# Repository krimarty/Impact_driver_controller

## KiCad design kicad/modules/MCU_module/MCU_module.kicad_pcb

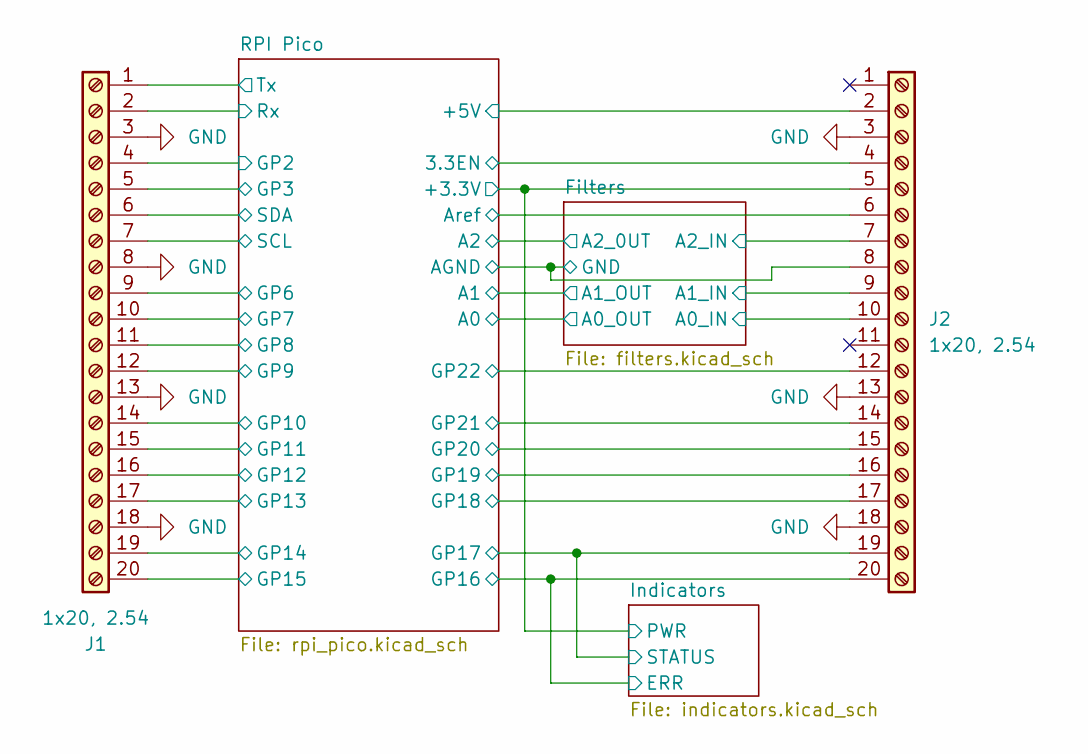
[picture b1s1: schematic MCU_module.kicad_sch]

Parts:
J1, J2: 1x20, 2.54; PinHeader_1x20_P2.54mm_Vertical; Manufacturer Part Number 68000-420HLF; Mouser number 649-68000-420HLF

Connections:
/Filters/A0_IN: J2.10; also elsewhere on the board
/Filters/A1_IN: J2.9; also elsewhere on the board
/Filters/A2_IN: J2.7; also elsewhere on the board
/Filters/GND: J2.8; also elsewhere on the board
/Indicators/ERR: J2.20; also elsewhere on the board
/Indicators/PWR: J2.5; also elsewhere on the board
/Indicators/STATUS: J2.19; also elsewhere on the board
/RPI Pico/3.3EN: J2.4; also elsewhere on the board
/RPI Pico/+5V: J2.2; also elsewhere on the board
/RPI Pico/Aref: J2.6; also elsewhere on the board
/RPI Pico/GP2: J1.4; also elsewhere on the board
/RPI Pico/GP3: J1.5; also elsewhere on the board
/RPI Pico/GP6: J1.9; also elsewhere on the board
/RPI Pico/GP7: J1.10; also elsewhere on the board
/RPI Pico/GP8: J1.11; also elsewhere on the board
/RPI Pico/GP9: J1.12; also elsewhere on the board
/RPI Pico/GP10: J1.14; also elsewhere on the board
/RPI Pico/GP11: J1.15; also elsewhere on the board
/RPI Pico/GP12: J1.16; also elsewhere on the board
/RPI Pico/GP13: J1.17; also elsewhere on the board
/RPI Pico/GP14: J1.19; also elsewhere on the board
/RPI Pico/GP15: J1.20; also elsewhere on the board
/RPI Pico/GP18: J2.17; also elsewhere on the board
/RPI Pico/GP19: J2.16; also elsewhere on the board
/RPI Pico/GP20: J2.15; also elsewhere on the board
/RPI Pico/GP21: J2.14; also elsewhere on the board
/RPI Pico/GP22: J2.12; also elsewhere on the board
/RPI Pico/Rx: J1.2; also elsewhere on the board
/RPI Pico/SCL: J1.7; also elsewhere on the board
/RPI Pico/SDA: J1.6; also elsewhere on the board
/RPI Pico/Tx: J1.1; also elsewhere on the board
GND: J1.3, J1.8, J1.13, J1.18, J2.3, J2.13, J2.18; also elsewhere on the board

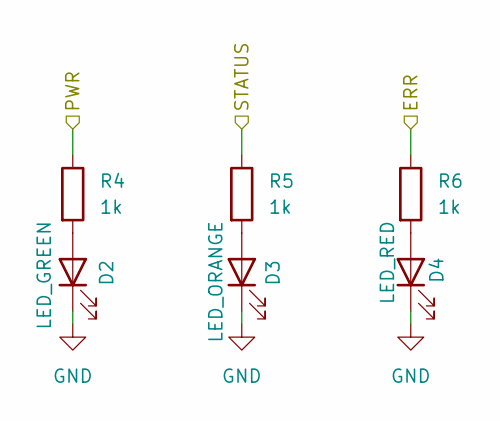
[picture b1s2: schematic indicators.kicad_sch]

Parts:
D2: LED_GREEN; LED_0805_2012Metric_Pad1.15x1.40mm_HandSolder; Manufacturer Part Number APTD2012LCGCK; Mouser number 604-APTD2012LCGCK
D3: LED_ORANGE; LED_0805_2012Metric_Pad1.15x1.40mm_HandSolder; Manufacturer Part Number APTD2012LSYCK; Mouser number 604-APTD2012LSYCK
D4: LED_RED; LED_0805_2012Metric_Pad1.15x1.40mm_HandSolder; Manufacturer Part Number APTD2012LSURCK; Mouser number 604-APTD2012LSURCK
R4, R5, R6: 1k; R_0603_1608Metric_Pad0.98x0.95mm_HandSolder; Manufacturer Part Number RC0603FR-071KL; Mouser number 603-RC0603FR-071KL

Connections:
/Indicators/ERR: R6.1; also elsewhere on the board
/Indicators/PWR: R4.1; also elsewhere on the board
/Indicators/STATUS: R5.1; also elsewhere on the board
GND: D2.1 (K), D3.1 (K), D4.1 (K); also elsewhere on the board
unnamed: D2.2 (A), R4.2
unnamed: D3.2 (A), R5.2
unnamed 38: D4.2 (A), R6.2; also elsewhere on the board

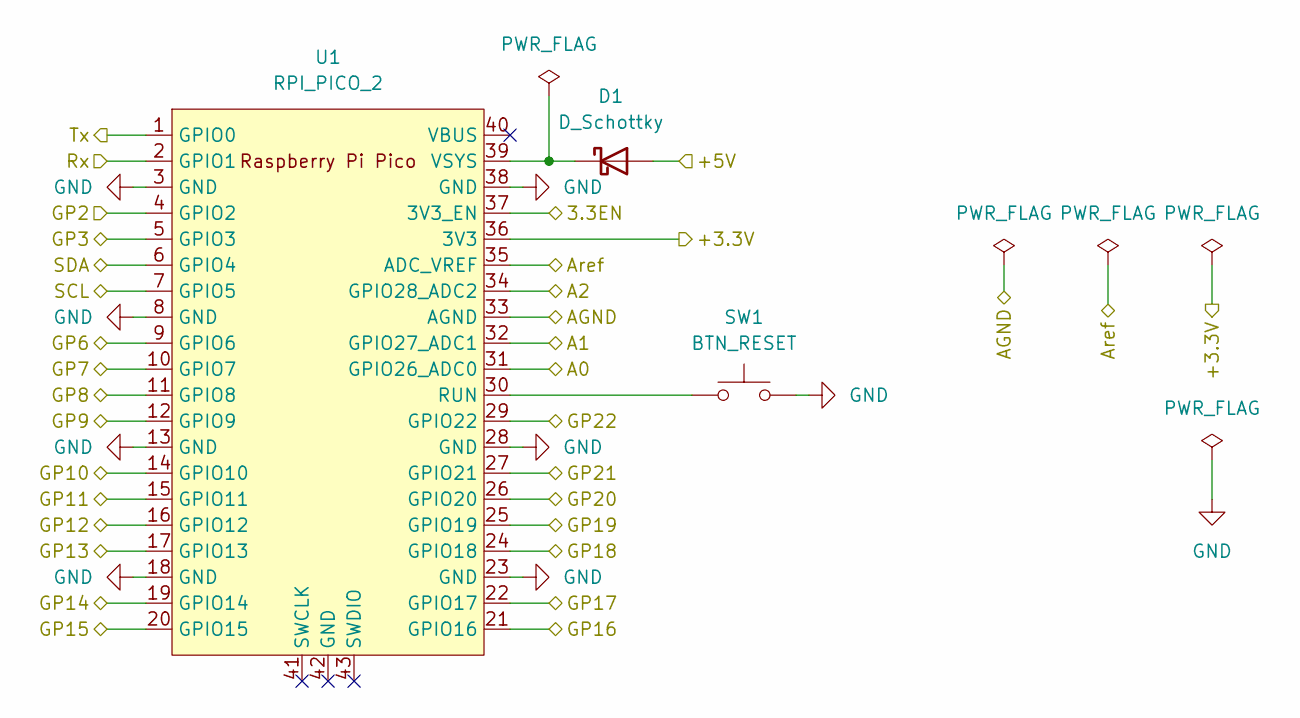
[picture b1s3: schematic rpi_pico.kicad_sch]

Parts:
D1: D_Schottky; D_0805_2012Metric_Pad1.15x1.40mm_HandSolder; Manufacturer Part Number SD0805S020S0R5; Mouser number 581-SD0805S020S0R5
SW1: BTN_RESET; SW_Tactile_SPST_NO_Straight_CK_PTS636Sx25SMTRLFS; Manufacturer Part Number TS09-63-25-WT-160-SMT-TR; Mouser number 179-TS0925WT160SMTTR
U1: RPI_PICO_2; RPi_Pico_SMD_TH; Manufacturer Part Number SC1631; Mouser number 358-SC1631

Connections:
/Filters/A0_OUT: U1.31 (GPIO26_ADC0); also elsewhere on the board
/Filters/A1_OUT: U1.32 (GPIO27_ADC1); also elsewhere on the board
/Filters/A2_0UT: U1.34 (GPIO28_ADC2); also elsewhere on the board
/Filters/GND: U1.33 (AGND); also elsewhere on the board
/Indicators/ERR: U1.21 (GPIO16); also elsewhere on the board
/Indicators/PWR: U1.36 (3V3); also elsewhere on the board
/Indicators/STATUS: U1.22 (GPIO17); also elsewhere on the board
/RPI Pico/3.3EN: U1.37 (3V3_EN); also elsewhere on the board
/RPI Pico/+5V: D1.2 (A); also elsewhere on the board
/RPI Pico/Aref: U1.35 (ADC_VREF); also elsewhere on the board
/RPI Pico/GP2: U1.4 (GPIO2); also elsewhere on the board
/RPI Pico/GP3: U1.5 (GPIO3); also elsewhere on the board
/RPI Pico/GP6: U1.9 (GPIO6); also elsewhere on the board
/RPI Pico/GP7: U1.10 (GPIO7); also elsewhere on the board
/RPI Pico/GP8: U1.11 (GPIO8); also elsewhere on the board
/RPI Pico/GP9: U1.12 (GPIO9); also elsewhere on the board
/RPI Pico/GP10: U1.14 (GPIO10); also elsewhere on the board
/RPI Pico/GP11: U1.15 (GPIO11); also elsewhere on the board
/RPI Pico/GP12: U1.16 (GPIO12); also elsewhere on the board
/RPI Pico/GP13: U1.17 (GPIO13); also elsewhere on the board
/RPI Pico/GP14: U1.19 (GPIO14); also elsewhere on the board
/RPI Pico/GP15: U1.20 (GPIO15); also elsewhere on the board
/RPI Pico/GP18: U1.24 (GPIO18); also elsewhere on the board
/RPI Pico/GP19: U1.25 (GPIO19); also elsewhere on the board
/RPI Pico/GP20: U1.26 (GPIO20); also elsewhere on the board
/RPI Pico/GP21: U1.27 (GPIO21); also elsewhere on the board
/RPI Pico/GP22: U1.29 (GPIO22); also elsewhere on the board
/RPI Pico/Rx: U1.2 (GPIO1); also elsewhere on the board
/RPI Pico/SCL: U1.7 (GPIO5); also elsewhere on the board
/RPI Pico/SDA: U1.6 (GPIO4); also elsewhere on the board
/RPI Pico/Tx: U1.1 (GPIO0); also elsewhere on the board
GND: SW1.2, U1.3 (GND), U1.8 (GND), U1.13 (GND), U1.18 (GND), U1.23 (GND), U1.28 (GND), U1.38 (GND); also elsewhere on the board
unnamed: D1.1 (K), U1.39 (VSYS)
unnamed: SW1.1, U1.30 (RUN)

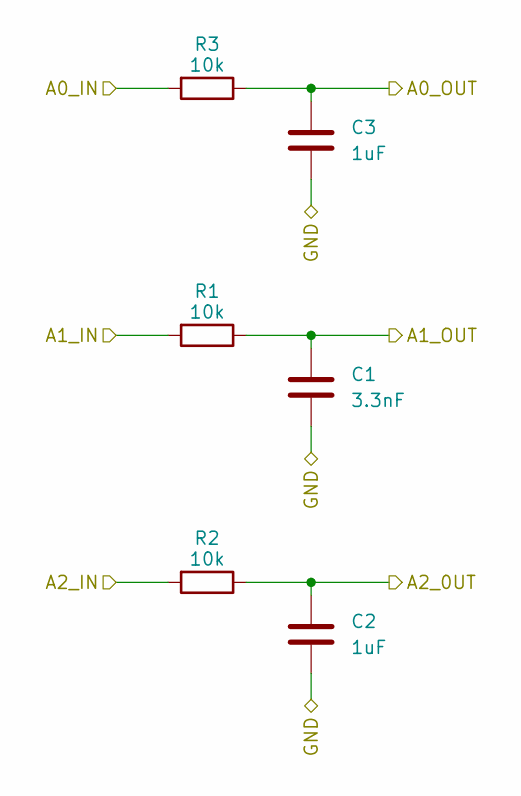
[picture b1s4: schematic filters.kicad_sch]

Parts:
C1: 3.3nF; C_0603_1608Metric_Pad1.08x0.95mm_HandSolder; Manufacturer Part Number VJ0603Y332KXBAC; Mouser number 77-VJ0603Y332KXBAC
C2, C3: 1uF; C_1206_3216Metric_Pad1.33x1.80mm_HandSolder; Manufacturer Part Number CC603KRX5R8BB105; Mouser number 603-CC603KRX5R8BB105
R1, R2, R3: 10k; R_0603_1608Metric_Pad0.98x0.95mm_HandSolder; Manufacturer Part Number RC0603FR-0710KL; Mouser number 603-RC0603FR-0710KL

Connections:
/Filters/A0_IN: R3.2; also elsewhere on the board
/Filters/A0_OUT: C3.1, R3.1; also elsewhere on the board
/Filters/A1_IN: R1.2; also elsewhere on the board
/Filters/A1_OUT: C1.1, R1.1; also elsewhere on the board
/Filters/A2_0UT: C2.1, R2.1; also elsewhere on the board
/Filters/A2_IN: R2.2; also elsewhere on the board
/Filters/GND: C1.2, C2.2, C3.2; also elsewhere on the board

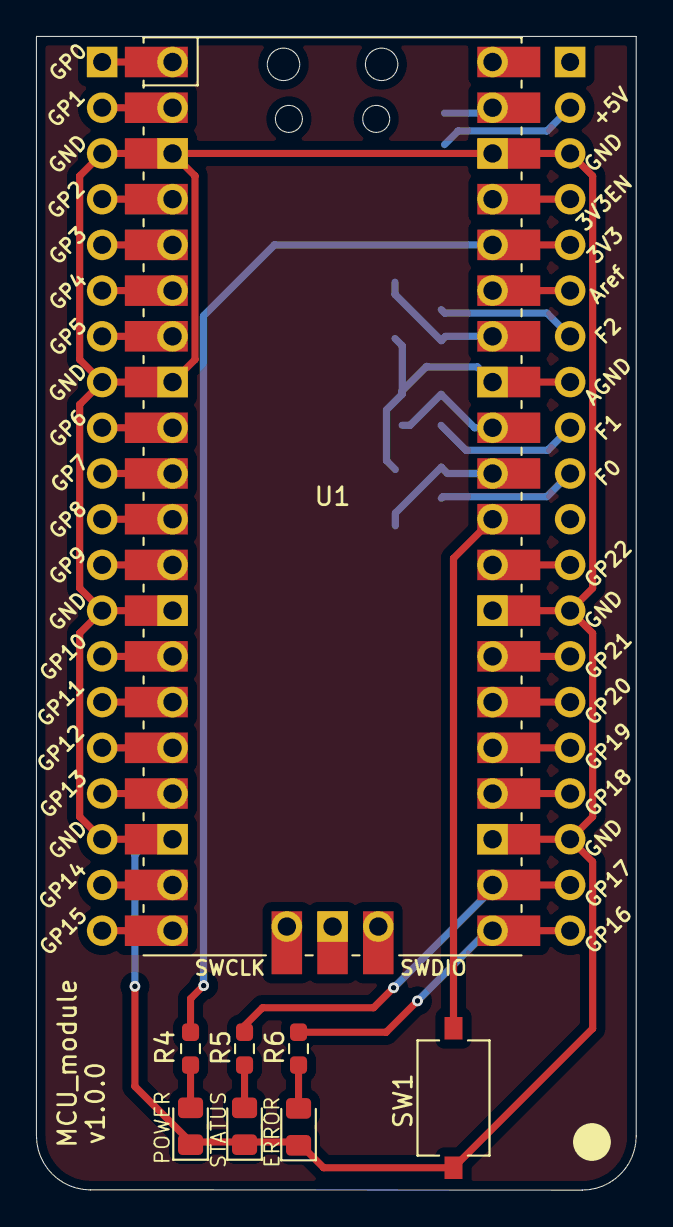
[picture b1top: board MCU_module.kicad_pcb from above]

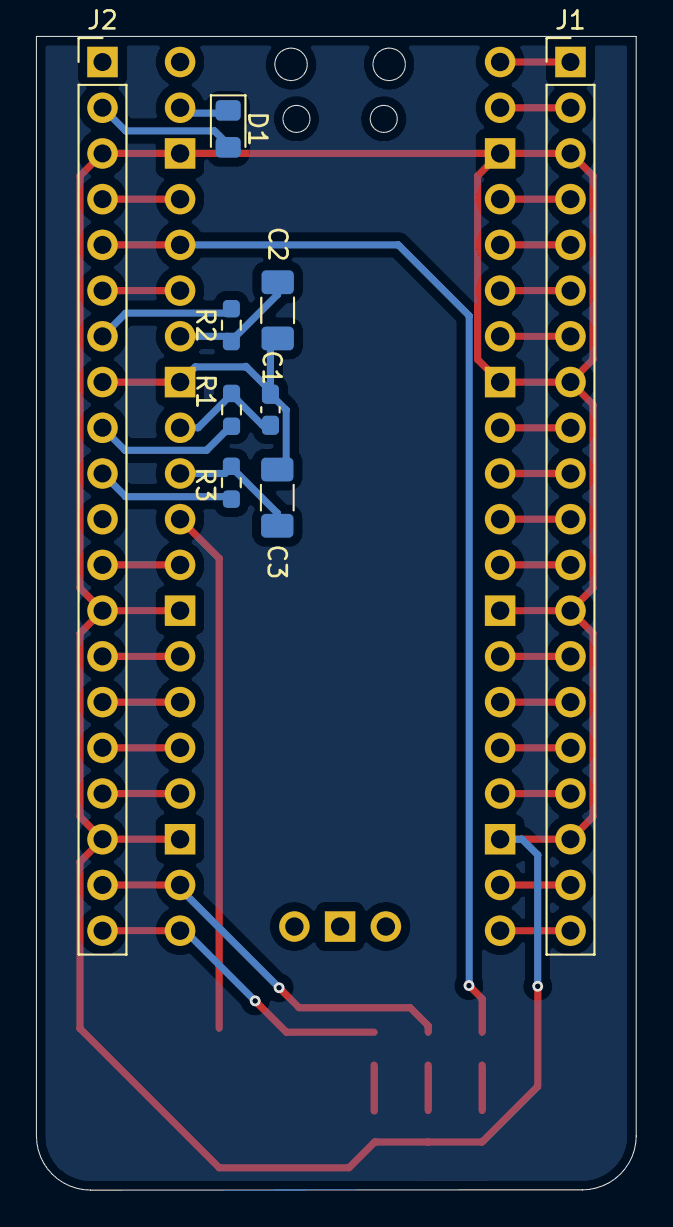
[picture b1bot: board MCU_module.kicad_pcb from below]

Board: 2 copper layers, 33.3 x 64.1 mm, 17 parts (9 on the bottom side), 40 nets.

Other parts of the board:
ERROR: LED_RED; LED_0805_2012Metric_Pad1.15x1.40mm_HandSolder

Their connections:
GND: ERROR.1 (K); also elsewhere on the board
unnamed 38: ERROR.2 (A); also elsewhere on the board

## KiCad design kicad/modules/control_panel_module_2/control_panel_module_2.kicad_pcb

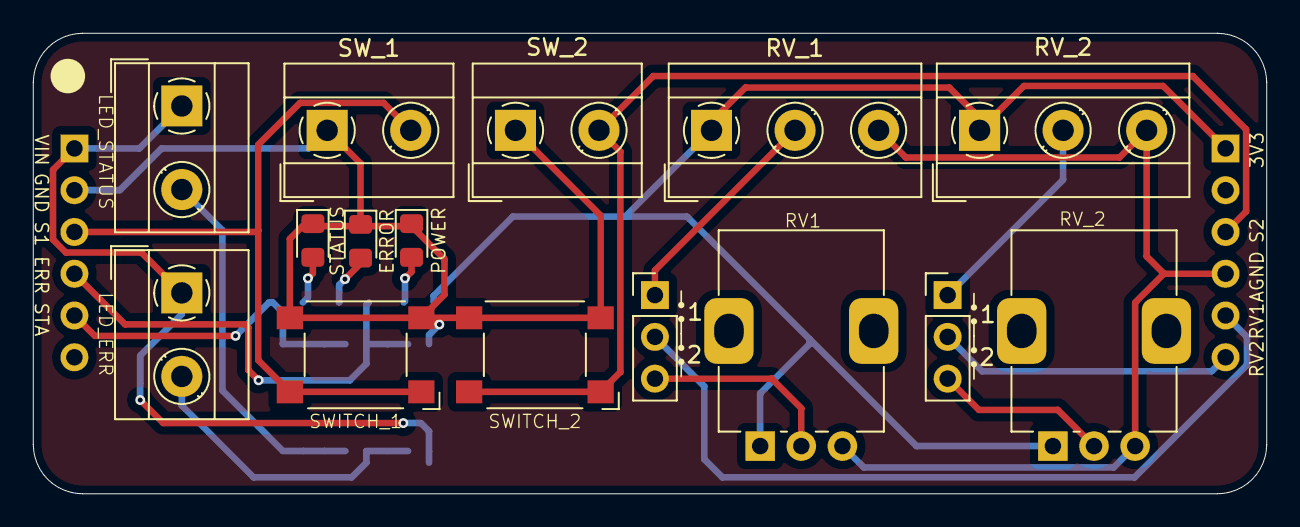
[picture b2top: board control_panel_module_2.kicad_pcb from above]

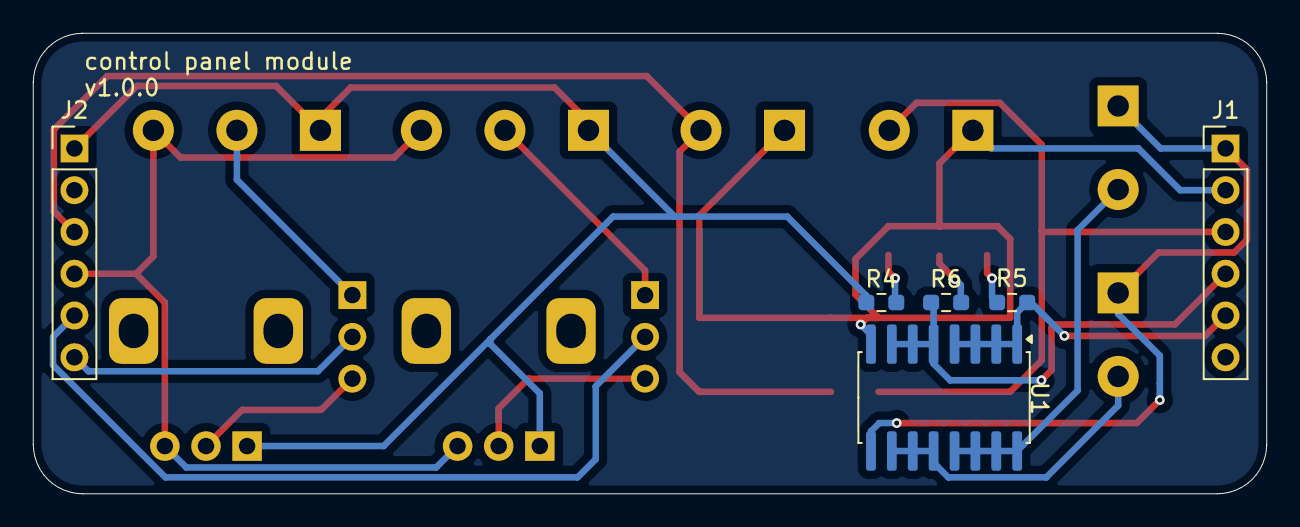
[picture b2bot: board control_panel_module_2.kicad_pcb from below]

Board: 2 copper layers, 75.0 x 28.0 mm, 21 parts (6 on the bottom side), 19 nets.

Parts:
ERROR: LED_RED; LED_0805_2012Metric_Pad1.15x1.40mm_HandSolder
J1, J2: 1x6 2.54; PinHeader_1x06_P2.54mm_Vertical
J3: 1x3 5.08; TerminalBlock_MetzConnect_Type101_RT01603HBWC_1x03_P5.08mm_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
J5, J7, J8: 1x2 5.08; TerminalBlock_MetzConnect_Type101_RT01602HBWC_1x02_P5.08mm_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
JP1, JP2: 1x3 2.54; PinHeader_1x03_P2.54mm_Vertical
POWER: LED_GREEN; LED_0805_2012Metric_Pad1.15x1.40mm_HandSolder
R4, R5, R6: 1k; R_0603_1608Metric_Pad0.98x0.95mm_HandSolder
RV1, RV2: 100k; Potentiometer_Alps_RK09K_Single_Vertical
RV_2: 1x3 5.08; TerminalBlock_MetzConnect_Type101_RT01603HBWC_1x03_P5.08mm_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
STATUS: LED_ORANGE; LED_0805_2012Metric_Pad1.15x1.40mm_HandSolder
SW2: BTN; SW_SPST_Omron_B3FS-105xP
SWITCH_1: BTN; SW_SPST_Omron_B3FS-105xP
SW_2: 1x2 5.08; TerminalBlock_MetzConnect_Type101_RT01602HBWC_1x02_P5.08mm_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
U1: ULN2004A; SOIC-16W_5.3x10.2mm_P1.27mm

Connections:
+3.3V: J2.1, J3.1, R4.1, RV1.1, RV2.1, RV_2.1
+Vin: J1.1, J7.1, J8.1, U1.9 (COM)
/Buttons/RV_1: J2.5, JP1.2 (C)
/Buttons/RV_2: J2.6, JP2.2 (C)
/Buttons/SW_1: J1.3, J5.2, SWITCH_1.1 (A)
/Buttons/SW_2: J2.3, SW2.1 (A), SW_2.2
/Indicators/ERR: J1.4, R6.1, U1.5 (I5), U1.6 (I6), U1.7 (I7)
/Indicators/STATUS: J1.5, R5.1, U1.1 (I1), U1.2 (I2), U1.3 (I3), U1.4 (I4)
AGND: J2.4, J3.3, RV1.3, RV2.3, RV_2.3
GND: ERROR.1 (K), J1.2, J5.1, POWER.1 (K), STATUS.1 (K), SW2.2 (B), SWITCH_1.2 (B), SW_2.1, U1.8 (GND)
unnamed: POWER.2 (A), R4.2
unnamed: R5.2, STATUS.2 (A)
unnamed: ERROR.2 (A), R6.2
unnamed: J3.2, JP1.1 (A)
unnamed: JP2.1 (A), RV_2.2
unnamed: J7.2, U1.13 (O4), U1.14 (O3), U1.15 (O2), U1.16 (O1)
unnamed: J8.2, U1.10 (O7), U1.11 (O6), U1.12 (O5)
unnamed: JP1.3 (B), RV1.2
unnamed: JP2.3 (B), RV2.2

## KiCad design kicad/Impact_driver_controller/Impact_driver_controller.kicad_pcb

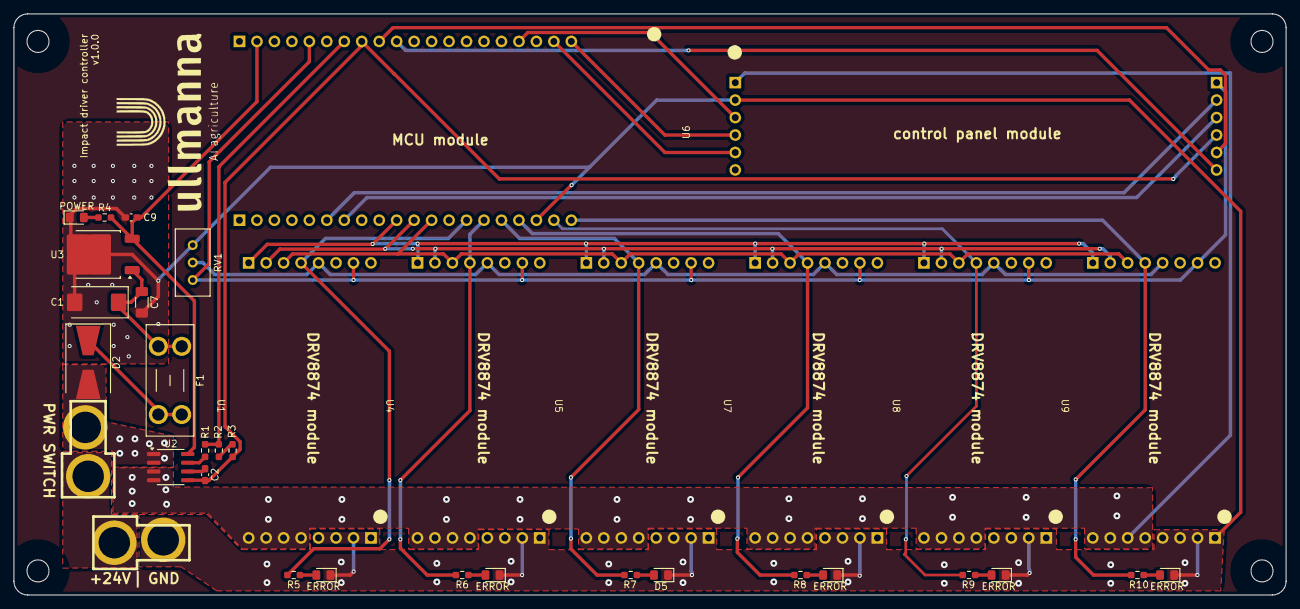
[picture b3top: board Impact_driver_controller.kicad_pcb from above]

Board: 2 copper layers, 185.0 x 84.5 mm, 40 parts (0 on the bottom side), 37 nets.

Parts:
C1: 100uF; CP_EIA-7343-40_Kemet-Y_Pad2.25x2.55mm_HandSolder
C2: 1nF; C_0603_1608Metric_Pad1.08x0.95mm_HandSolder
C7: 0.47uF; C_1206_3216Metric_Pad1.33x1.80mm_HandSolder
C9: 0.1uF; C_0603_1608Metric_Pad1.08x0.95mm_HandSolder
D2: SS34; D_SMB-SMC_Universal_Handsoldering
D5: LED_RED; LED_0805_2012Metric_Pad1.15x1.40mm_HandSolder
ERROR: LED_RED; LED_0805_2012Metric_Pad1.15x1.40mm_HandSolder
ERROR#2, ERROR#3, ERROR#4, ERROR#5: LED_RED; LED_0805_2012Metric_Pad1.15x1.40mm_HandSolder
F1: FUSE 1A; Fuseholder_Blade_Mini_Keystone_3568
H3, H3#2, H3#3, H3#4: MountingHole; MountingHole_3.2mm_M3
J1, J2: 1x2 TDEAN; DEANS
POWER: LED_GREEN; LED_0805_2012Metric_Pad1.15x1.40mm_HandSolder
R1, R2, R3: 10k; R_0603_1608Metric_Pad0.98x0.95mm_HandSolder
R4, R5, R6, R7, R8, R9, R10: 1k; R_0603_1608Metric_Pad0.98x0.95mm_HandSolder
RV1: 100k; Potentiometer_Bourns_3296W_Vertical
U1, U4, U5, U7, U8, U9: DRV8874_module
U2: ACS71230A; SOIC-8_3.9x4.9mm_P1.27mm
U3: LM78M05; TO-252-2
U6: MCU_module
U10: Control_panel_module; control_panel_module

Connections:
+3.3V: RV1.1, U1.7 (+Vcc), U4.7 (+Vcc), U5.7 (+Vcc), U6.36 (3V3), U7.7 (+Vcc), U8.7 (+Vcc), U9.7 (+Vcc), U10.7 (+3.3V)
+5V: C9.1, R4.2, U2.8 (VCC), U3.3 (VO), U6.39 (+5V)
+VDD: U1.10 (VIN), U2.3 (IP-), U2.4 (IP-), U4.10 (VIN), U5.10 (VIN), U7.10 (VIN), U8.10 (VIN), U9.10 (VIN), U10.1 (Vin)
/Current probe/IN: D2.2 (A), J2.2, U2.1 (IP+), U2.2 (IP+)
/Current probe/I_MEAS: R1.1, R2.2, U6.34 (F2)
/Drivers/+Vref: RV1.2, U1.5 (+Vref), U4.5 (+Vref), U5.5 (+Vref), U7.5 (+Vref), U8.5 (+Vref), U9.5 (+Vref)
/Drivers/EN: U1.1 (EN), U4.1 (EN), U5.1 (EN), U6.10 (GPIO7), U7.1 (EN), U8.1 (EN), U9.1 (EN)
/Drivers/FAULT_1: R5.1, U1.4 (FAULT), U6.14 (GPIO10)
/Drivers/FAULT_2: R6.1, U4.4 (FAULT), U6.15 (GPIO11)
/Drivers/FAULT_3: R7.1, U5.4 (FAULT), U6.16 (GPIO12)
/Drivers/FAULT_4: R8.1, U6.17 (GPIO13), U7.4 (FAULT)
/Drivers/FAULT_5: R9.1, U6.19 (GPIO14), U8.4 (FAULT)
/Drivers/FAULT_6: R10.1, U6.20 (GPIO15), U9.4 (FAULT)
/Drivers/PH: U1.2 (PH), U4.2 (PH), U5.2 (PH), U6.11 (GPIO8), U7.2 (PH), U8.2 (PH), U9.2 (PH)
/Drivers/SLEEP: U1.3 (SLEEP), U4.3 (SLEEP), U5.3 (SLEEP), U6.12 (GPIO9), U7.3 (SLEEP), U8.3 (SLEEP), U9.3 (SLEEP)
/Power supply/+V_IN: J1.1, J2.1
AGND: C2.2, R3.1, U2.5 (GND), U6.33 (AGND), U10.10 (AGND)
GND: C1.2, C7.2, C9.2, D5.1 (K), ERROR.1 (K), ERROR#2.1 (K), ERROR#3.1 (K), ERROR#4.1 (K), ERROR#5.1 (K), J1.2, POWER.1 (K), RV1.3, U1.9 (GND), U3.2 (GND), U4.9 (GND), U5.9 (GND), U6.18 (GND), U7.9 (GND), U8.9 (GND), U9.9 (GND), U10.2 (GND)
unnamed: ERROR#5.2 (A), R5.2
unnamed: D2.1 (K), F1.2
unnamed: ERROR.2 (A), R6.2
unnamed: POWER.2 (A), R4.1
unnamed: D5.2 (A), R7.2
unnamed: ERROR#2.2 (A), R8.2
unnamed: ERROR#4.2 (A), R9.2
unnamed: ERROR#3.2 (A), R10.2
unnamed: R2.1, R3.2
unnamed: C2.1, U2.6 (FILTER)
unnamed: R1.2, U2.7 (VIOUT)
unnamed: C1.1, C7.1, F1.1, U3.1 (VI)
unnamed: U6.21 (GPIO16), U10.4 (LED_ERR)
unnamed: U6.22 (GPIO17), U10.5 (LED_STATUS)
unnamed: U6.32 (F1), U10.11 (RV1)
unnamed: U6.31 (F0), U10.12 (RV2)
unnamed: U6.24 (GPIO18), U10.3 (SW_MODE)
SCL: U6.7 (GPIO5), U10.9 (SCL)
SDA: U6.6 (GPIO4), U10.8 (SDA)

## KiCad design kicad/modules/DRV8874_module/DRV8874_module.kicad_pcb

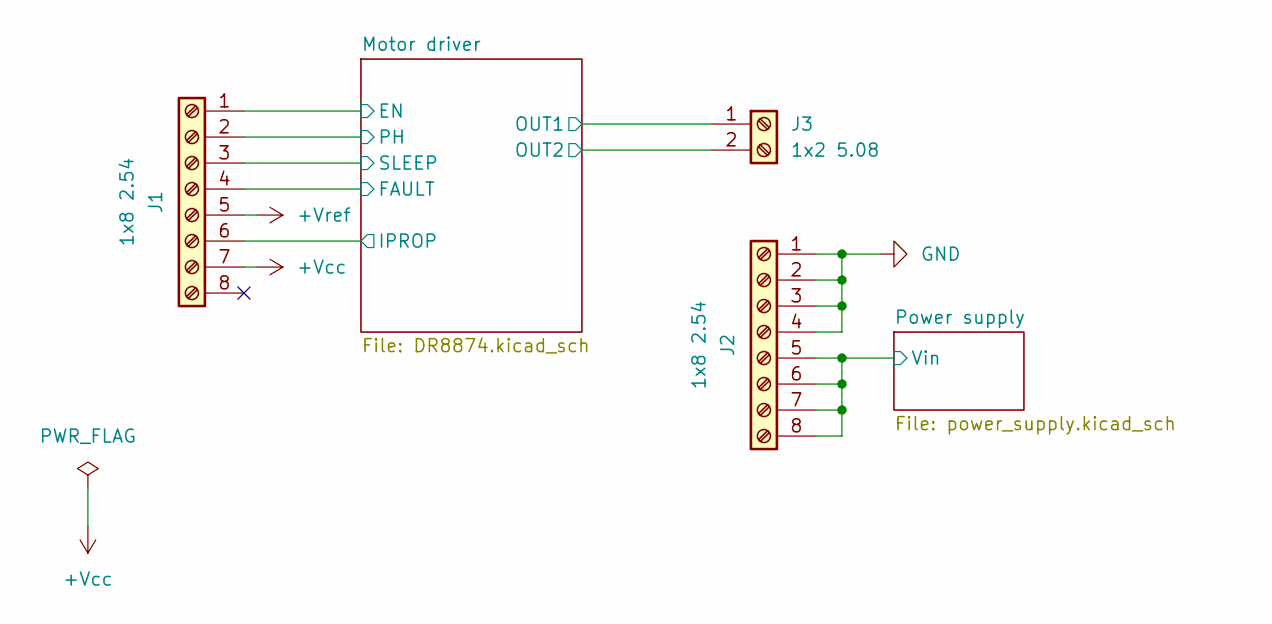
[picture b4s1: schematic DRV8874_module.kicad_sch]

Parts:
J1, J2: 1x8 2.54; PinHeader_1x08_P2.54mm_Vertical; Manufacturer Part Number 68000-420HLF; Mouser number 649-68000-420HLF
J3: 1x2 5.08; TerminalBlock_RND_205-00232_1x02_P5.08mm_Horizontal; Manufacturer Part Number TB0012-508-02GR; Mouser number 179-TB0012-508-02GR

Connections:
+Vcc: J1.7; also elsewhere on the board
+Vref: J1.5; also elsewhere on the board
/Motor driver/EN: J1.1; also elsewhere on the board
/Motor driver/FAULT: J1.4; also elsewhere on the board
/Motor driver/IPROP: J1.6; also elsewhere on the board
/Motor driver/OUT1: J3.1; also elsewhere on the board
/Motor driver/OUT2: J3.2; also elsewhere on the board
/Motor driver/PH: J1.2; also elsewhere on the board
/Motor driver/SLEEP: J1.3; also elsewhere on the board
/Power supply/Vin: J2.5, J2.6, J2.7, J2.8; also elsewhere on the board
GND: J2.1, J2.2, J2.3, J2.4; also elsewhere on the board

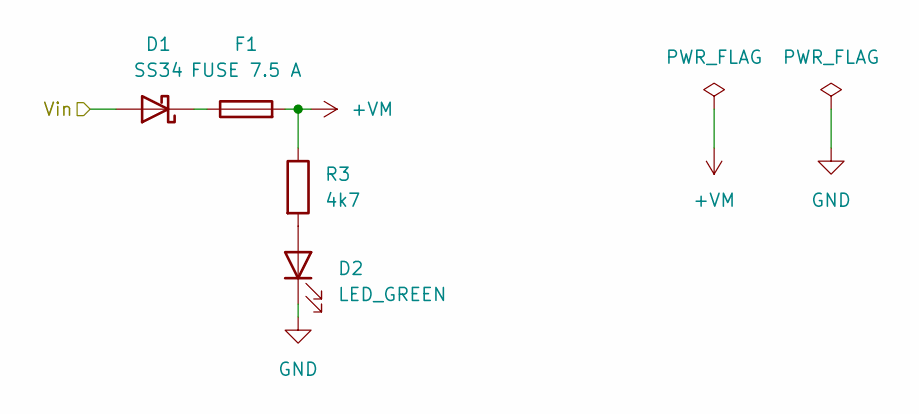
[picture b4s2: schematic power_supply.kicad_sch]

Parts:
D1: SS34; D_SMB-SMC_Universal_Handsoldering; Manufacturer Part Number SS34; Mouser number 512-SS34
D2: LED_GREEN; LED_0805_2012Metric_Pad1.15x1.40mm_HandSolder; Manufacturer Part Number APTD2012LCGCK; Mouser number 604-APTD2012LCGCK
F1: FUSE 7.5 A; Fuseholder_Blade_Mini_Keystone_3568; Manufacturer Part Number 3568; Mouser number 534-3568
R3: 4k7; R_0603_1608Metric_Pad0.98x0.95mm_HandSolder; Manufacturer Part Number RC0603FR-074K7L; Mouser number 603-RC0603FR-074K7L

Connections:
+VM: F1.2, R3.1; also elsewhere on the board
/Power supply/Vin: D1.2 (A); also elsewhere on the board
GND: D2.1 (K); also elsewhere on the board
unnamed: D1.1 (K), F1.1
unnamed: D2.2 (A), R3.2

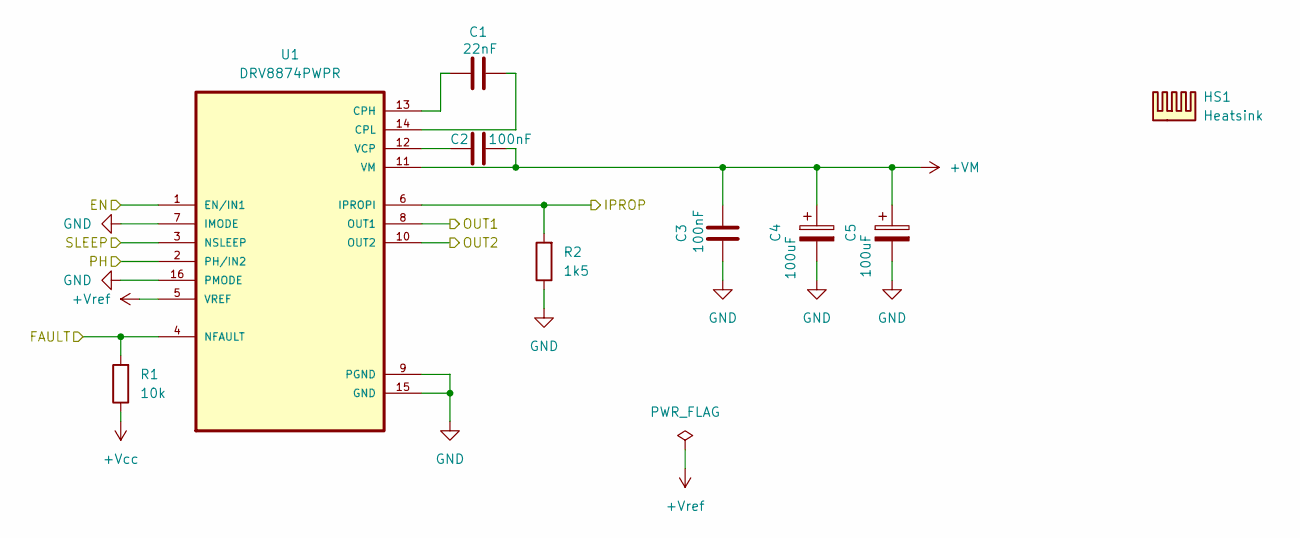
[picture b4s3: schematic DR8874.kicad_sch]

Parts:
C1: 22nF; C_0603_1608Metric_Pad1.08x0.95mm_HandSolder; Manufacturer Part Number CC0603JRX7R9BB223; Mouser number 603-CC603JRX7R9BB223
C2, C3: 100nF; C_0603_1608Metric_Pad1.08x0.95mm_HandSolder; Manufacturer Part Number C0603C104M5RACTU; Mouser number 603-CC603KRX7R9BB103
C4, C5: 100uF; CP_EIA-7343-40_Kemet-Y_Pad2.25x2.55mm_HandSolder; Manufacturer Part Number 80-T491X107M25ATAUTO; Mouser number 80-T491X107M25ATAUTO
HS1: Heatsink; DRV8874_TO220_Heatsink; Manufacturer Part Number ICKSMDM21SA
R1: 10k; R_0603_1608Metric_Pad0.98x0.95mm_HandSolder; Manufacturer Part Number RC0603FR-0710KL; Mouser number 603-RC0603FR-0710KL
R2: 1k5; R_0603_1608Metric_Pad0.98x0.95mm_HandSolder; Manufacturer Part Number MCT0603MD1501BP500; Mouser number 594-MCT0603MD1501BP5
U1: DRV8874PWPR; SOP65P640X120-17N; Manufacturer Part Number DRV8874PWPR; Mouser number 595-DRV8874PWPR

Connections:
+VM: C2.1, C3.1, C4.1, C5.1, U1.11 (VM); also elsewhere on the board
+Vcc: R1.1; also elsewhere on the board
+Vref: U1.5 (VREF); also elsewhere on the board
/Motor driver/EN: U1.1 (EN/IN1); also elsewhere on the board
/Motor driver/FAULT: R1.2, U1.4 (NFAULT); also elsewhere on the board
/Motor driver/IPROP: R2.2, U1.6 (IPROPI); also elsewhere on the board
/Motor driver/OUT1: U1.8 (OUT1); also elsewhere on the board
/Motor driver/OUT2: U1.10 (OUT2); also elsewhere on the board
/Motor driver/PH: U1.2 (PH/IN2); also elsewhere on the board
/Motor driver/SLEEP: U1.3 (NSLEEP); also elsewhere on the board
GND: C3.2, C4.2, C5.2, R2.1, U1.7 (IMODE), U1.9 (PGND), U1.15 (GND), U1.16 (PMODE), U1.17; also elsewhere on the board
unnamed: C1.2, U1.13 (CPH)
unnamed: C1.1, U1.14 (CPL)
unnamed: C2.2, U1.12 (VCP)

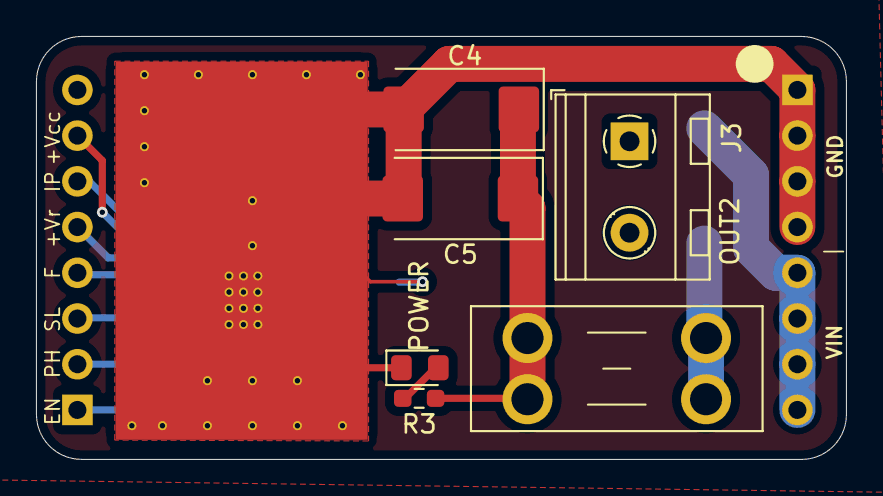
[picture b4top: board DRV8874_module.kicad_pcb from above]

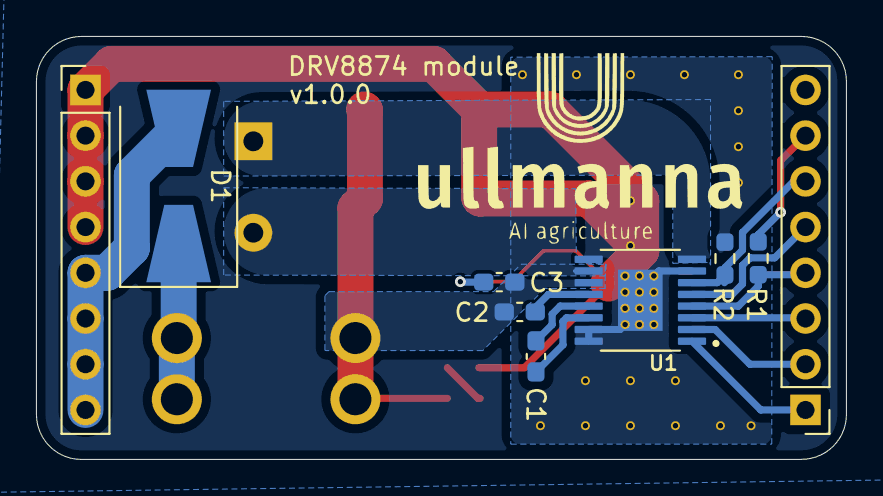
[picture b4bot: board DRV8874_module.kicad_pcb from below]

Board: 2 copper layers, 45.0 x 23.5 mm, 16 parts (9 on the bottom side), 17 nets.

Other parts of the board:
HEATSINK: DRV8874_Heatsink_21x14; DRV8874_TO220_Heatsink

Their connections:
GND: HEATSINK.GND; also elsewhere on the board

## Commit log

2025-09-04 half bridge + power wiring
2025-09-04 add current probe
2025-09-05 Add I/O
2025-09-10 Add MCU module
2025-09-10 control panel schematic
2025-09-11 add control panel module
2025-09-13 Main board schematic
2025-09-13 First main board layout
2025-09-13 Main board wiring
2025-09-14 main board silkscreen
2025-09-14 dots for orientation
2025-09-16 Connector for bigger current, control module 2
2025-09-17 Add part numbers
2025-09-20 BOM with Ullmanna part numbers
2025-09-26 LED footprint update
2025-09-26 Started software development
2025-09-28 Add control panel classes
2025-09-28 Add current probe class
2025-09-29 Remove invalid CSV path
2026-01-12 Version withnout sleep pins
2026-01-21 Add new version of software
2026-01-21 Add hardcoded running time
